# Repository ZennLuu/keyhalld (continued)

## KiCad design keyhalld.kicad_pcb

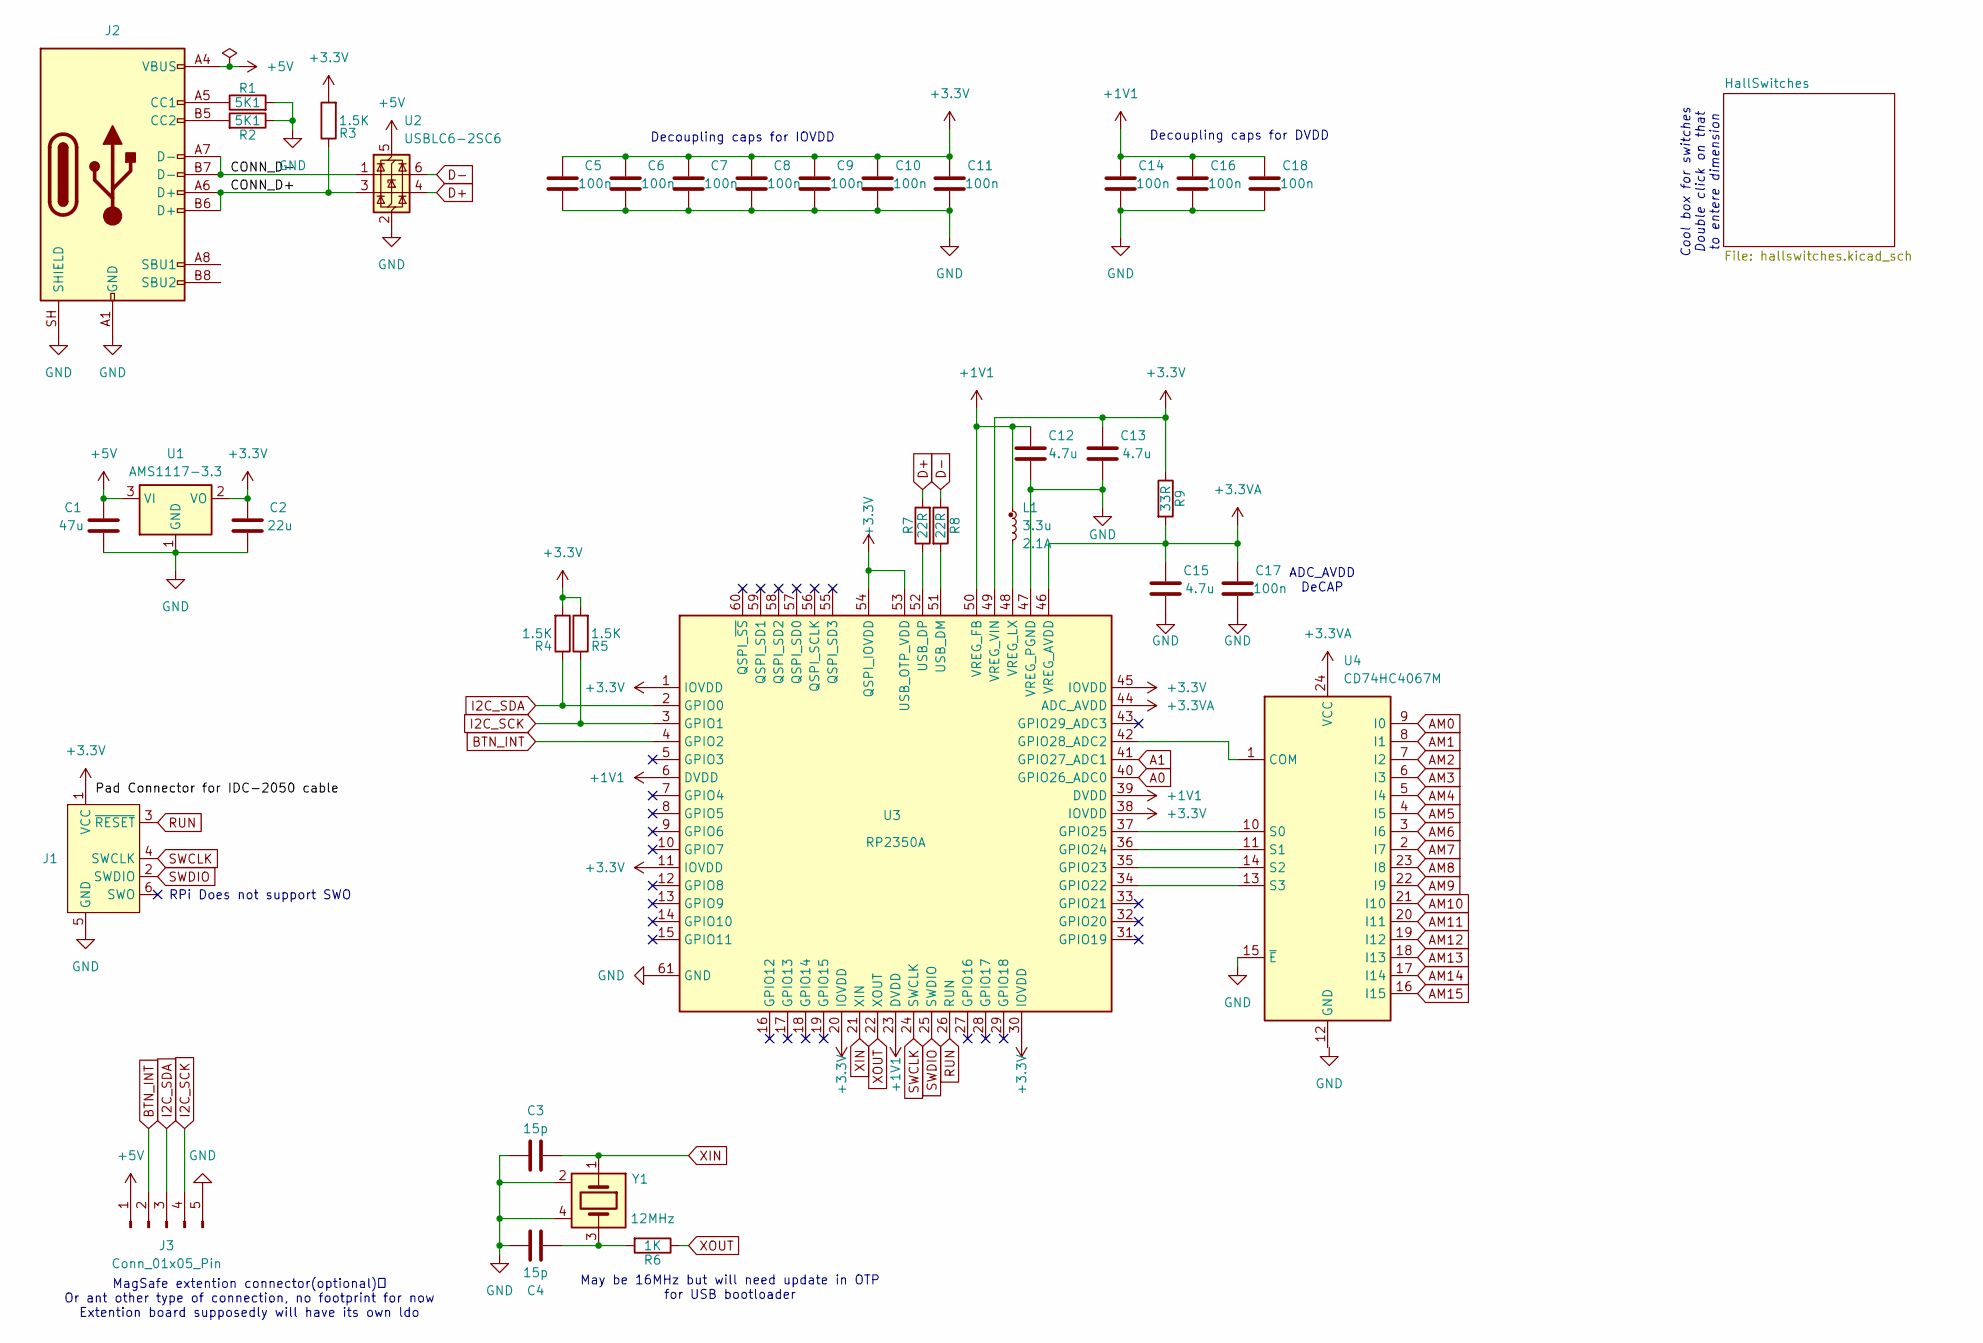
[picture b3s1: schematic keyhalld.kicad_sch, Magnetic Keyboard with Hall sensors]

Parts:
C1: 47u; C_0603_1608Metric_Pad1.08x0.95mm_HandSolder
C2: 22u; C_0603_1608Metric_Pad1.08x0.95mm_HandSolder
C3, C4: 15p; C_0603_1608Metric_Pad1.08x0.95mm_HandSolder
C5, C6, C7, C8, C9, C10, C11, C14, C16, C17, C18: 100n; C_0603_1608Metric_Pad1.08x0.95mm_HandSolder
C12, C13, C15: 4.7u; C_0603_1608Metric_Pad1.08x0.95mm_HandSolder
J1: Conn_ARM_SWD_TagConnect_TC2030-NL; Tag-Connect_TC2030-IDC-NL_2x03_P1.27mm_Vertical
J2: USB_C_Receptacle_USB2.0_16P; USB_C_Receptacle_GCT_USB4105-xx-A_16P_TopMnt_Horizontal
J3: Conn_01x05_Pin
L1: 3.3u; abracon_aota-b201610s3r3-101-t; tolerance 20%; part_uid RP-01GY5D-2VC7WP
R1, R2: 5K1; R_0603_1608Metric_Pad0.98x0.95mm_HandSolder
R3, R4, R5: 1.5K; R_0603_1608Metric_Pad0.98x0.95mm_HandSolder
R6: 1K; R_0603_1608Metric_Pad0.98x0.95mm_HandSolder
R7, R8: 22R; R_0603_1608Metric_Pad0.98x0.95mm_HandSolder
R9: 33R; R_0603_1608Metric_Pad0.98x0.95mm_HandSolder
U1: AMS1117-3.3; SOT-223-3_TabPin2
U2: USBLC6-2SC6; SOT-23-6
U3: RP2350A; rpi_rp2350a_vias; part_uid RP-01HA9H-9K5E8T
U4: CD74HC4067M; SOIC-24W_7.5x15.4mm_P1.27mm
Y1: 12MHz; Oscillator_SMD_Abracon_ASE-4Pin_3.2x2.5mm; tolerance 30ppm; part_uid RP-01G8X7-GS352B

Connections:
+1V1: C12.1, C14.1, C16.1, C18.1, L1.1, U3.6 (DVDD), U3.23 (DVDD), U3.39 (DVDD), U3.50 (VREG_FB)
+3.3V: C2.1, C5.1, C6.1, C7.1, C8.1, C9.1, C10.1, C11.1, C13.1, J1.1 (VCC), R3.2, R4.2, R5.2, R9.1, U1.2 (VO), U3.1 (IOVDD), U3.11 (IOVDD), U3.20 (IOVDD), U3.30 (IOVDD), U3.38 (IOVDD), U3.45 (IOVDD), U3.49 (VREG_VIN), U3.53 (USB_OTP_VDD), U3.54 (QSPI_IOVDD)
+3.3VA: C15.1, C17.1, R9.2, U3.44 (ADC_AVDD), U3.46 (VREG_AVDD), U4.24 (VCC); also elsewhere on the board
+5V: C1.1, J2.A4 (VBUS), J2.A9 (VBUS), J2.B4 (VBUS), J2.B9 (VBUS), J3.1, U1.3 (VI), U2.5 (VBUS)
/CONN_D+: J2.A6 (D+), J2.B6 (D+), R3.1, U2.3 (I/O2)
/CONN_D-: J2.A7 (D-), J2.B7 (D-), U2.1 (I/O1)
A0: U3.40 (GPIO26_ADC0); also elsewhere on the board
A1: U3.41 (GPIO27_ADC1); also elsewhere on the board
AM0: U4.9 (I0); also elsewhere on the board
AM1: U4.8 (I1); also elsewhere on the board
AM2: U4.7 (I2); also elsewhere on the board
AM3: U4.6 (I3); also elsewhere on the board
AM4: U4.5 (I4); also elsewhere on the board
AM5: U4.4 (I5); also elsewhere on the board
AM6: U4.3 (I6); also elsewhere on the board
AM7: U4.2 (I7); also elsewhere on the board
AM8: U4.23 (I8); also elsewhere on the board
AM9: U4.22 (I9); also elsewhere on the board
AM10: U4.21 (I10); also elsewhere on the board
AM11: U4.20 (I11); also elsewhere on the board
AM12: U4.19 (I12); also elsewhere on the board
AM13: U4.18 (I13); also elsewhere on the board
AM14: U4.17 (I14); also elsewhere on the board
AM15: U4.16 (I15); also elsewhere on the board
BTN_INT: J3.2, U3.4 (GPIO2)
D+: R7.2, U2.4 (I/O2)
D-: R8.1, U2.6 (I/O1)
GND: C1.2, C2.2, C3.1, C4.1, C5.2, C6.2, C7.2, C8.2, C9.2, C10.2, C11.2, C12.2, C13.2, C14.2, C15.2, C16.2, C17.2, C18.2, J1.5 (GND), J2.A1 (GND), J2.A12 (GND), J2.B1 (GND), J2.B12 (GND), J2.SH (SHIELD), J3.5, R1.2, R2.1, U1.1 (GND), U2.2 (GND), U3.47 (VREG_PGND), U3.61 (GND), U4.15 (~E), Y1.2, Y1.4; also elsewhere on the board
I2C_SCK: J3.4, R5.1, U3.3 (GPIO1)
I2C_SDA: J3.3, R4.1, U3.2 (GPIO0)
unnamed: C4.2, R6.2, Y1.3
unnamed: J2.A5 (CC1), R1.1
unnamed: J2.B5 (CC2), R2.2
unnamed: U3.34 (GPIO22), U4.13 (S3)
unnamed: U3.35 (GPIO23), U4.14 (S2)
unnamed: U3.36 (GPIO24), U4.11 (S1)
unnamed: U3.37 (GPIO25), U4.10 (S0)
unnamed: U3.42 (GPIO28_ADC2), U4.1 (COM)
unnamed: R8.2, U3.51 (USB_DM)
unnamed: R7.1, U3.52 (USB_DP)
unnamed: L1.2, U3.48 (VREG_LX)
RUN: J1.3 (~RESET), U3.26 (RUN)
SWCLK: J1.4 (SWCLK), U3.24 (SWCLK)
SWDIO: J1.2 (SWDIO), U3.25 (SWDIO)
XIN: C3.2, U3.21 (XIN), Y1.1
XOUT: R6.1, U3.22 (XOUT)

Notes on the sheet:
RPi Does not support SWO
MagSafe extention connector(optional)🧲 Or ant other type of connection, no footprint for now Extention board supposedly will have its own ldo
May be 16MHz but will need update in OTP for USB bootloader
ADC_AVDD DeCAP
Cool box for switches Double click on that to entere dimension
Decoupling caps for DVDD
Decoupling caps for IOVDD

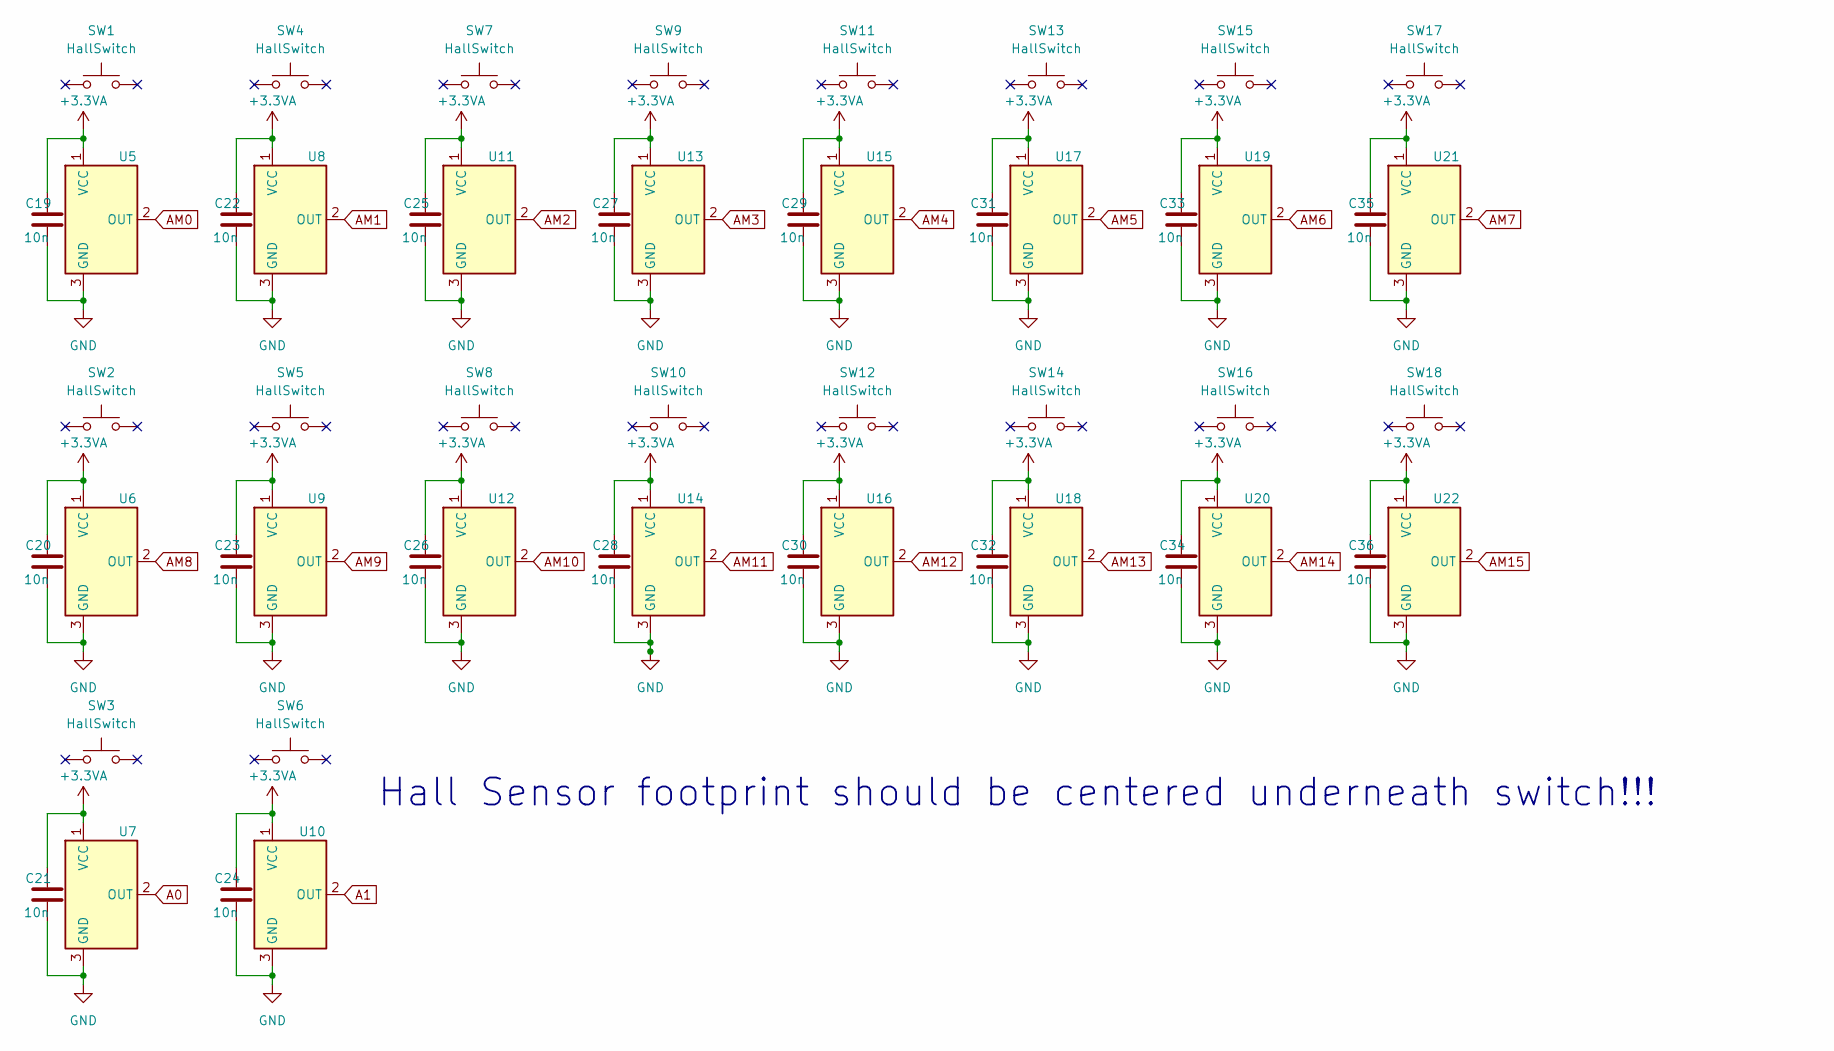
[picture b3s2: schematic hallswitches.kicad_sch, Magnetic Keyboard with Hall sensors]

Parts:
C19, C20, C21, C22, C23, C24, C25, C26, C27, C28, C29, C30, C31, C32, C33, C34, C35, C36: 10n; C_0603_1608Metric_Pad1.08x0.95mm_HandSolder
SW1, SW2, SW3, SW4, SW5, SW6, SW7, SW8, SW9, SW10, SW11, SW12, SW13, SW14, SW15, SW16, SW17, SW18: HallSwitch; Custom_MX_PCB_1.00u
U5, U6, U7, U8, U9, U10, U11, U12, U13, U14, U15, U16, U17, U18, U19, U20, U21, U22: DRV5055A4xDBZxQ1; SOT-23

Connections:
+3.3VA: C19.2, C20.2, C21.2, C22.2, C23.2, C24.2, C25.2, C26.2, C27.2, C28.2, C29.2, C30.2, C31.2, C32.2, C33.2, C34.2, C35.2, C36.2, U5.1 (VCC), U6.1 (VCC), U7.1 (VCC), U8.1 (VCC), U9.1 (VCC), U10.1 (VCC), U11.1 (VCC), U12.1 (VCC), U13.1 (VCC), U14.1 (VCC), U15.1 (VCC), U16.1 (VCC), U17.1 (VCC), U18.1 (VCC), U19.1 (VCC), U20.1 (VCC), U21.1 (VCC), U22.1 (VCC); also elsewhere on the board
A0: U7.2 (OUT); also elsewhere on the board
A1: U10.2 (OUT); also elsewhere on the board
AM0: U5.2 (OUT); also elsewhere on the board
AM1: U8.2 (OUT); also elsewhere on the board
AM2: U11.2 (OUT); also elsewhere on the board
AM3: U13.2 (OUT); also elsewhere on the board
AM4: U15.2 (OUT); also elsewhere on the board
AM5: U17.2 (OUT); also elsewhere on the board
AM6: U19.2 (OUT); also elsewhere on the board
AM7: U21.2 (OUT); also elsewhere on the board
AM8: U6.2 (OUT); also elsewhere on the board
AM9: U9.2 (OUT); also elsewhere on the board
AM10: U12.2 (OUT); also elsewhere on the board
AM11: U14.2 (OUT); also elsewhere on the board
AM12: U16.2 (OUT); also elsewhere on the board
AM13: U18.2 (OUT); also elsewhere on the board
AM14: U20.2 (OUT); also elsewhere on the board
AM15: U22.2 (OUT); also elsewhere on the board
GND: C19.1, C20.1, C21.1, C22.1, C23.1, C24.1, C25.1, C26.1, C27.1, C28.1, C29.1, C30.1, C31.1, C32.1, C33.1, C34.1, C35.1, C36.1, U5.3 (GND), U6.3 (GND), U7.3 (GND), U8.3 (GND), U9.3 (GND), U10.3 (GND), U11.3 (GND), U12.3 (GND), U13.3 (GND), U14.3 (GND), U15.3 (GND), U16.3 (GND), U17.3 (GND), U18.3 (GND), U19.3 (GND), U20.3 (GND), U21.3 (GND), U22.3 (GND); also elsewhere on the board

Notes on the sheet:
Hall Sensor footprint should be centered underneath switch!!!

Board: 4 copper layers, 89 parts (0 on the bottom side), 45 nets, no tracks yet.
